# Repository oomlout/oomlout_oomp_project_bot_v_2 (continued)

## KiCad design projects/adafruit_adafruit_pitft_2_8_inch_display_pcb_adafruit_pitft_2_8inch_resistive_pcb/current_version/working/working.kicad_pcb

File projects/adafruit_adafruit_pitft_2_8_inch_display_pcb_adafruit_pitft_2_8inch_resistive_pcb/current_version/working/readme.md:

# adafruit_pitft_2_8_inch_display_pcb
 
## summary 
* id: adafruit_adafruit_pitft_2_8_inch_display_pcb_adafruit_pitft_2_8inch_resistive_pcb
* user: adafruit
* name: adafruit_pitft_2_8_inch_display_pcb
* board: adafruit_pitft_2_8inch_resistive_pcb
* repo: https://github.com/adafruit/Adafruit-PiTFT-2.8-inch-Display-PCB

* src_file_repo_sch: 
* src_file_repo_sch_link: https://github.com/adafruit/Adafruit-PiTFT-2.8-inch-Display-PCB/tree/master/
* full details link: https://github.com/oomlout/oomlout_oomp_project_bot_v_2/tree/main/projects/adafruit_adafruit_pitft_2_8_inch_display_pcb_adafruit_pitft_2_8inch_resistive_pcb/current_version/working  

## schematic  
  
[schematic (pdf)](working_schematic.pdf) 

## pcb  

[board (pdf)](working.pdf)  

## working_bom
| Id | Designator | Footprint | Quantity | Designation | Supplier and ref |  | None | 
| --- | --- | --- | --- | --- | --- | --- | --- | 
| 1 | C3,C2,C4 | C0805K | 3 | 0.1uF |  |  | [''] | 
| 2 | R6,R7,R8 | R0805 | 3 | 10K |  |  | [''] | 
| 3 | Q1 | SOT23-BEC | 1 | MMBT2222 |  |  | [''] | 
| 4 | R11,R10 | R0805 | 2 | 22 |  |  | [''] | 
| 5 | R1,R3,R2,R4 | R0805 | 4 | 100 |  |  | [''] | 
| 6 | C5,C1 | C0805K | 2 | 10uF |  |  | [''] | 
| 7 | IC4 | SOT23-5L | 1 | MIC5225-3.3 |  |  | [''] | 
| 8 | U$10,U$11,U$18 | FIDUCIAL_1MM | 3 | FIDUCIAL |  |  | [''] | 
| 9 | R9,R5 | R0805 | 2 | 1K |  |  | [''] | 
| 10 | U2 | QFN16_3MM | 1 | STMPE610 |  |  | [''] | 
| 11 | IC5 | SOT23 | 1 | AXP803 |  |  | [''] | 
| 12 | JP1 | 2X13 | 1 |  |  |  | [''] | 
| 13 | U$16,U$17,U$15 | MOUNTINGHOLE_2.5_PLATED_THICK | 3 | MOUNTINGHOLE2.5_THICK |  |  | [''] | 
| 14 | U$2 | TFT_2.83IN_240X320_50PIN | 1 | DISP_LCD_1.28IN_240X320_50PIN |  |  | [''] | 
| 15 | SW1,SW2,SW4,SW3 | TACT_PANA-EVQ | 4 |  |  |  | [''] | 
| 16 | U$3 | RASPBERRYPIV2_SHIELD | 1 | RASPBERRYPI_B_MODELB_V2 |  |  | [''] | 
| 17 | U$23 | ADAFRUIT_TEXT_20MM | 1 |  |  |  | [''] | 

## bom_schematic
| Ref | Qnty | Value | Cmp name | Footprint | Description | Vendor | DNP | 
| --- | --- | --- | --- | --- | --- | --- | --- | 
| C1, C5 | 2 | 10uF | C-USC0805K | working:C0805K |  |  |  | 
| C2, C3, C4 | 3 | 0.1uF | C-USC0805K | working:C0805K |  |  |  | 
| IC4 | 1 | LP298XS | LP298XS | working:SOT23-5L |  |  |  | 
| IC5 | 1 | AXP803 | AXP083-SAG | working:SOT23 |  |  |  | 
| JP1 | 1 | HEADER-2X13 | HEADER-2X13 | working:2X13 |  |  |  | 
| Q1 | 1 | MMBT2222 | -NPN-SOT23-BEC | working:SOT23-BEC |  |  |  | 
| R1, R2, R3, R4 | 4 | 100 | R-US_R0805 | working:R0805 |  |  |  | 
| R5, R9 | 2 | 1K | R-US_R0805 | working:R0805 |  |  |  | 
| R6, R7, R8 | 3 | 10K | R-US_R0805 | working:R0805 |  |  |  | 
| R10, R11 | 2 | 22 | R-US_R0805 | working:R0805 |  |  |  | 
| SW1, SW2, SW3, SW4 | 4 | SWITCH_PUSHBUTTONEVQ-PE | SWITCH_PUSHBUTTONEVQ-PE | working:TACT_PANA-EVQ |  |  |  | 
| U2 | 1 | STMPE610 | STMPE610 | working:QFN16_3MM |  |  |  | 
| U$2 | 1 | DISP_LCD_1.28IN_240X320_50PIN | DISP_LCD_1.28IN_240X320_50PIN | working:TFT_2.83IN_240X320_50PIN |  |  |  | 
| U$3 | 1 | RASPBERRYPI_B_MODELB_V2 | RASPBERRYPI_B_MODELB_V2 | working:RASPBERRYPIV2_SHIELD |  |  |  | 
| U$10, U$11, U$18 | 3 | FIDUCIAL | FIDUCIAL | working:FIDUCIAL_1MM |  |  |  | 
| U$15, U$16, U$17 | 3 | MOUNTINGHOLE2.5_THICK | MOUNTINGHOLE2.5_THICK | working:MOUNTINGHOLE_2.5_PLATED_THICK |  |  |  |

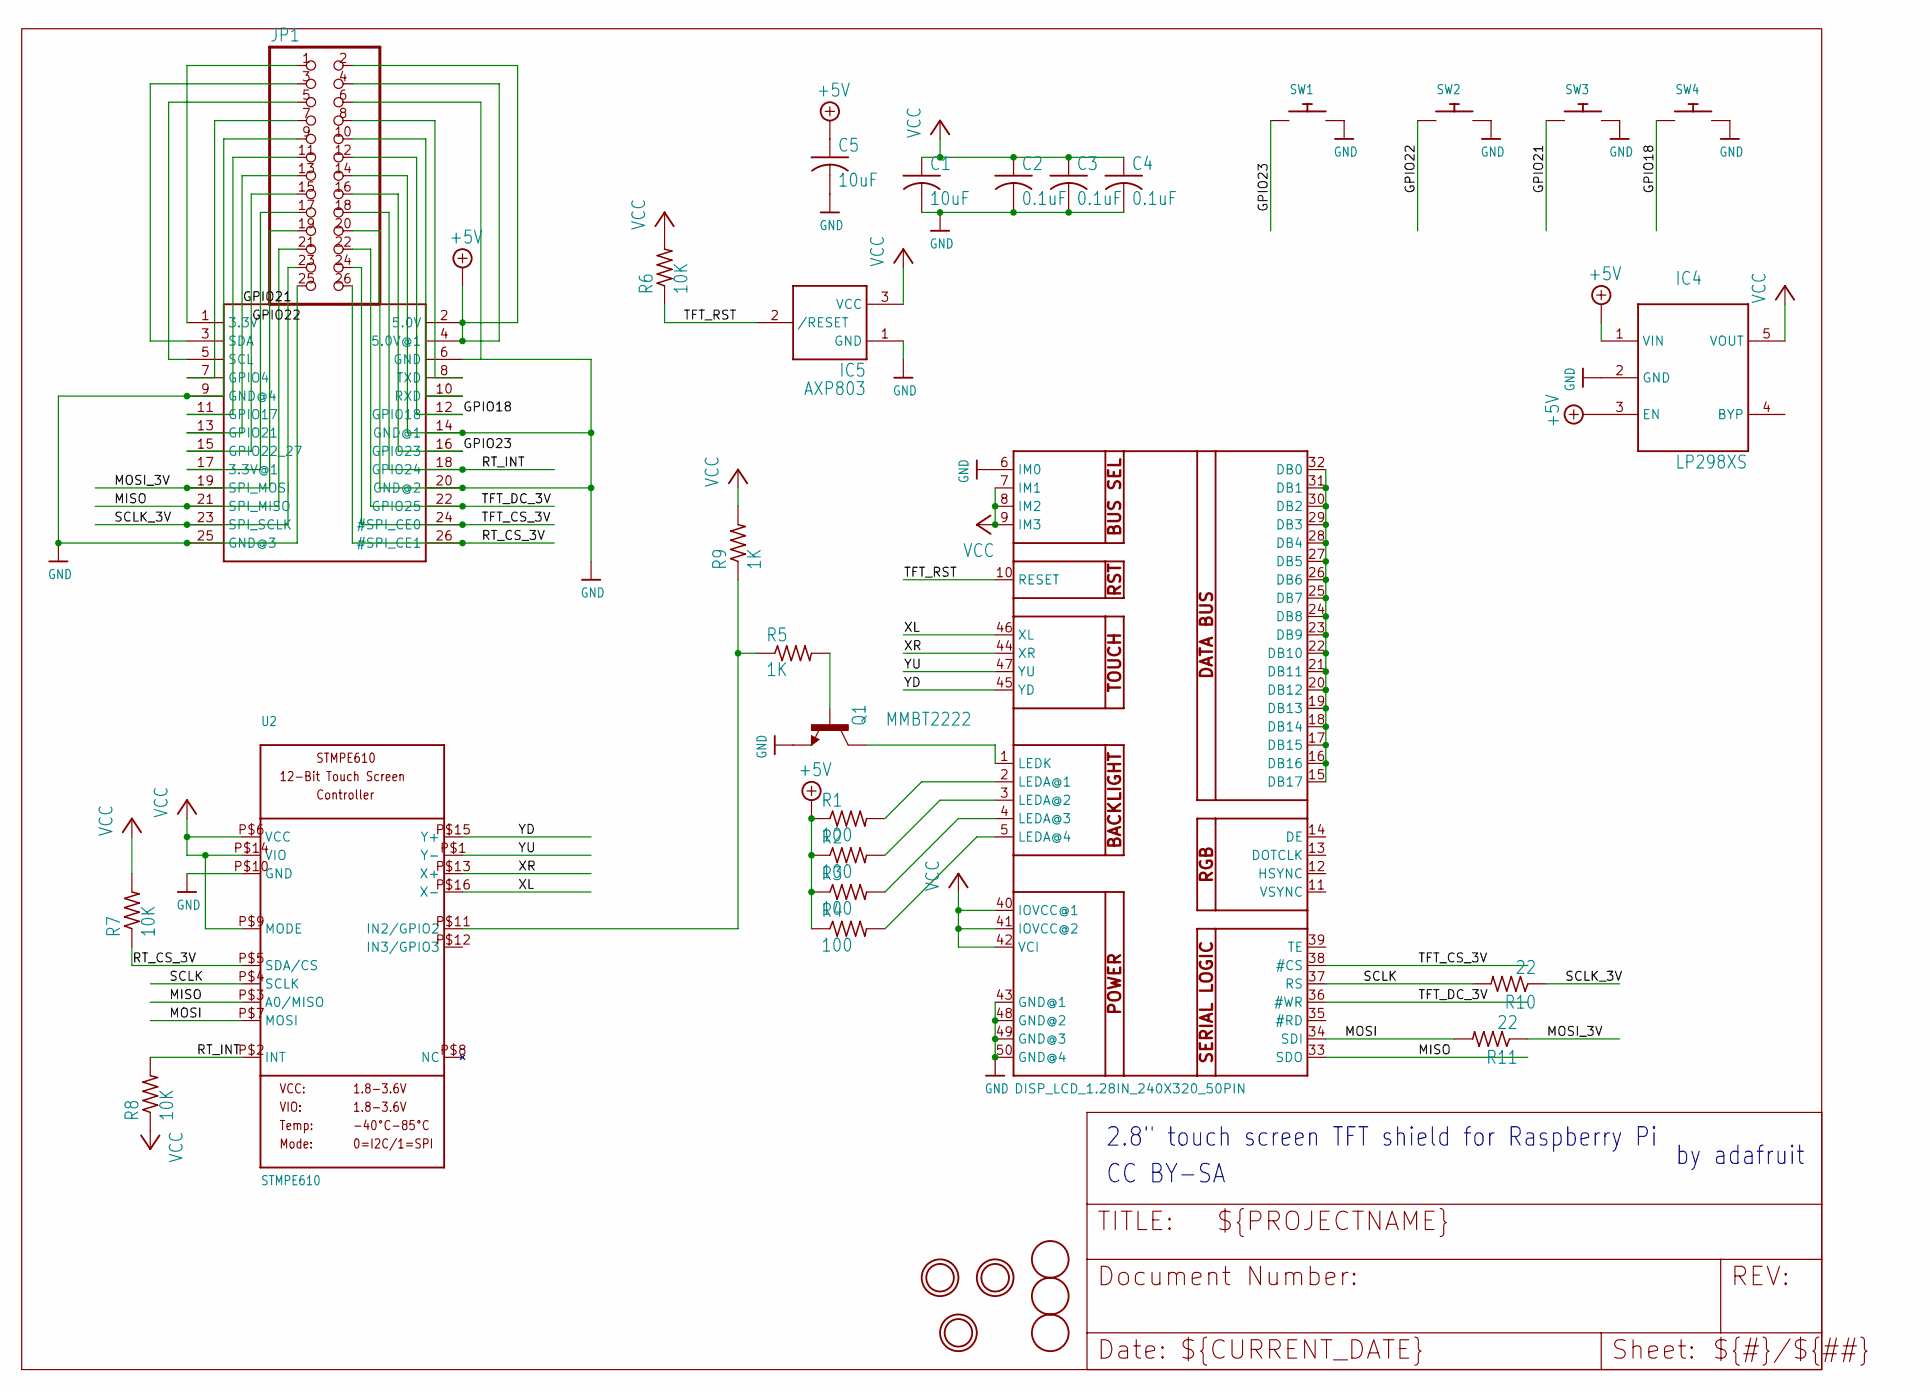
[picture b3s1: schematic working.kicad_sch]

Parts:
C1, C5: 10uF; C0805K
C2, C3, C4: 0.1uF; C0805K
IC4: LP298XS; SOT23-5L
IC5: AXP803; SOT23
JP1: HEADER-2X13; 2X13
Q1: MMBT2222; SOT23-BEC
R1, R2, R3, R4: 100; R0805
R5, R9: 1K; R0805
R6, R7, R8: 10K; R0805
R10, R11: 22; R0805
SW1, SW2, SW3, SW4: SWITCH_PUSHBUTTONEVQ-PE; TACT_PANA-EVQ
U2: STMPE610; QFN16_3MM
U$2: DISP_LCD_1.28IN_240X320_50PIN; TFT_2.83IN_240X320_50PIN
U$3: RASPBERRYPI_B_MODELB_V2; RASPBERRYPIV2_SHIELD
U$10, U$11, U$18: FIDUCIAL; FIDUCIAL_1MM
U$15, U$16, U$17: MOUNTINGHOLE2.5_THICK; MOUNTINGHOLE_2.5_PLATED_THICK

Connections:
3.3V: JP1.1, U$3.1 (3.3V)
3.3V@2: JP1.17, U$3.17 (3.3V@1)
+5V: C5.1, IC4.1 (VIN), IC4.3 (EN), JP1.2, JP1.4, R1.1, R2.1, R3.1, R4.1, U$3.2 (5.0V), U$3.4 (5.0V@1)
GND: C1.2, C2.2, C3.2, C4.2, C5.2, IC4.2 (GND), IC5.1 (GND), JP1.6, JP1.9, JP1.14, JP1.20, JP1.25, Q1.E, SW1.P$2, SW2.P$2, SW3.P$2, SW4.P$2, U2.P$10 (GND), U$2.6 (IM0), U$2.43 (GND@1), U$2.48 (GND@2), U$2.49 (GND@3), U$2.50 (GND@4), U$3.6 (GND), U$3.9 (GND@4), U$3.14 (GND@1), U$3.20 (GND@2), U$3.25 (GND@3)
GPIO18: JP1.12, SW4.P$1, U$3.12 (GPIO18)
GPIO21: JP1.13, SW3.P$1, U$3.13 (GPIO21)
GPIO22: JP1.15, SW2.P$1, U$3.15 (GPIO22_27)
GPIO23: JP1.16, SW1.P$1, U$3.16 (GPIO23)
MISO: JP1.21, U2.P$3 (A0/MISO), U$2.33 (SDO), U$3.21 (SPI_MISO)
MOSI: R11.2, U2.P$7 (MOSI), U$2.34 (SDI)
MOSI_3V: JP1.19, R11.1, U$3.19 (SPI_MOSI)
unnamed: Q1.C, U$2.1 (LEDK)
unnamed: R1.2, U$2.2 (LEDA@1)
unnamed: R2.2, U$2.3 (LEDA@2)
unnamed: R3.2, U$2.4 (LEDA@3)
unnamed: R5.1, R9.1, U2.P$11 (IN2/GPIO2)
unnamed: JP1.3, U$3.3 (SDA)
unnamed: JP1.5, U$3.5 (SCL)
unnamed: JP1.7, U$3.7 (GPIO4)
unnamed: U$2.15 (DB17), U$2.16 (DB16), U$2.17 (DB15), U$2.18 (DB14), U$2.19 (DB13), U$2.20 (DB12), U$2.21 (DB11), U$2.22 (DB10), U$2.23 (DB9), U$2.24 (DB8), U$2.25 (DB7), U$2.26 (DB6), U$2.27 (DB5), U$2.28 (DB4), U$2.29 (DB3), U$2.30 (DB2), U$2.31 (DB1), U$2.32 (DB0)
unnamed: R4.2, U$2.5 (LEDA@4)
unnamed: JP1.11, U$3.11 (GPIO17)
unnamed: Q1.B, R5.2
unnamed: JP1.10, U$3.10 (RXD)
unnamed: JP1.8, U$3.8 (TXD)
RT_CS_3V: JP1.26, R7.1, U2.P$5 (SDA/CS), U$3.26 (#SPI_CE1)
RT_INT: JP1.18, R8.2, U2.P$2 (INT), U$3.18 (GPIO24)
SCLK: R10.2, U2.P$4 (SCLK), U$2.37 (RS)
SCLK_3V: JP1.23, R10.1, U$3.23 (SPI_SCLK)
TFT_CS_3V: JP1.24, U$2.38 (#CS), U$3.24 (#SPI_CE0)
TFT_DC_3V: JP1.22, U$2.36 (#WR), U$3.22 (GPIO25)
TFT_RST: IC5.2 (/RESET), R6.1, U$2.10 (RESET)
VCC: C1.1, C2.1, C3.1, C4.1, IC4.5 (VOUT), IC5.3 (VCC), R6.2, R7.2, R8.1, R9.2, U2.P$6 (VCC), U2.P$9 (MODE), U2.P$14 (VIO), U$2.7 (IM1), U$2.8 (IM2), U$2.9 (IM3), U$2.40 (IOVCC@1), U$2.41 (IOVCC@2), U$2.42 (VCI)
XL: U2.P$16 (X-), U$2.46 (XL)
XR: U2.P$13 (X+), U$2.44 (XR)
YD: U2.P$15 (Y+), U$2.45 (YD)
YU: U2.P$1 (Y-), U$2.47 (YU)

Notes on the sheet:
CC BY-SA
by adafruit~{}
2.8" touch screen TFT shield for Raspberry Pi

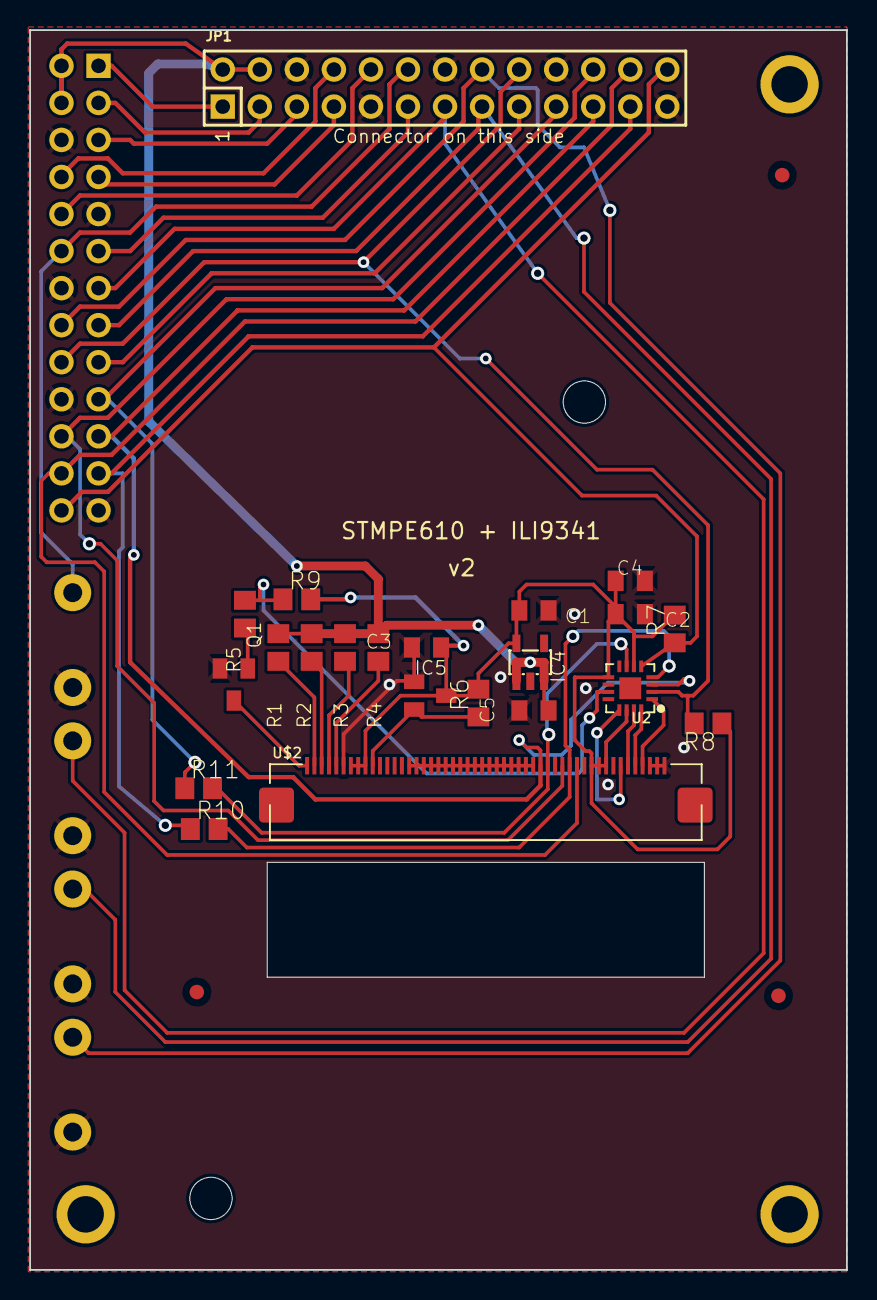
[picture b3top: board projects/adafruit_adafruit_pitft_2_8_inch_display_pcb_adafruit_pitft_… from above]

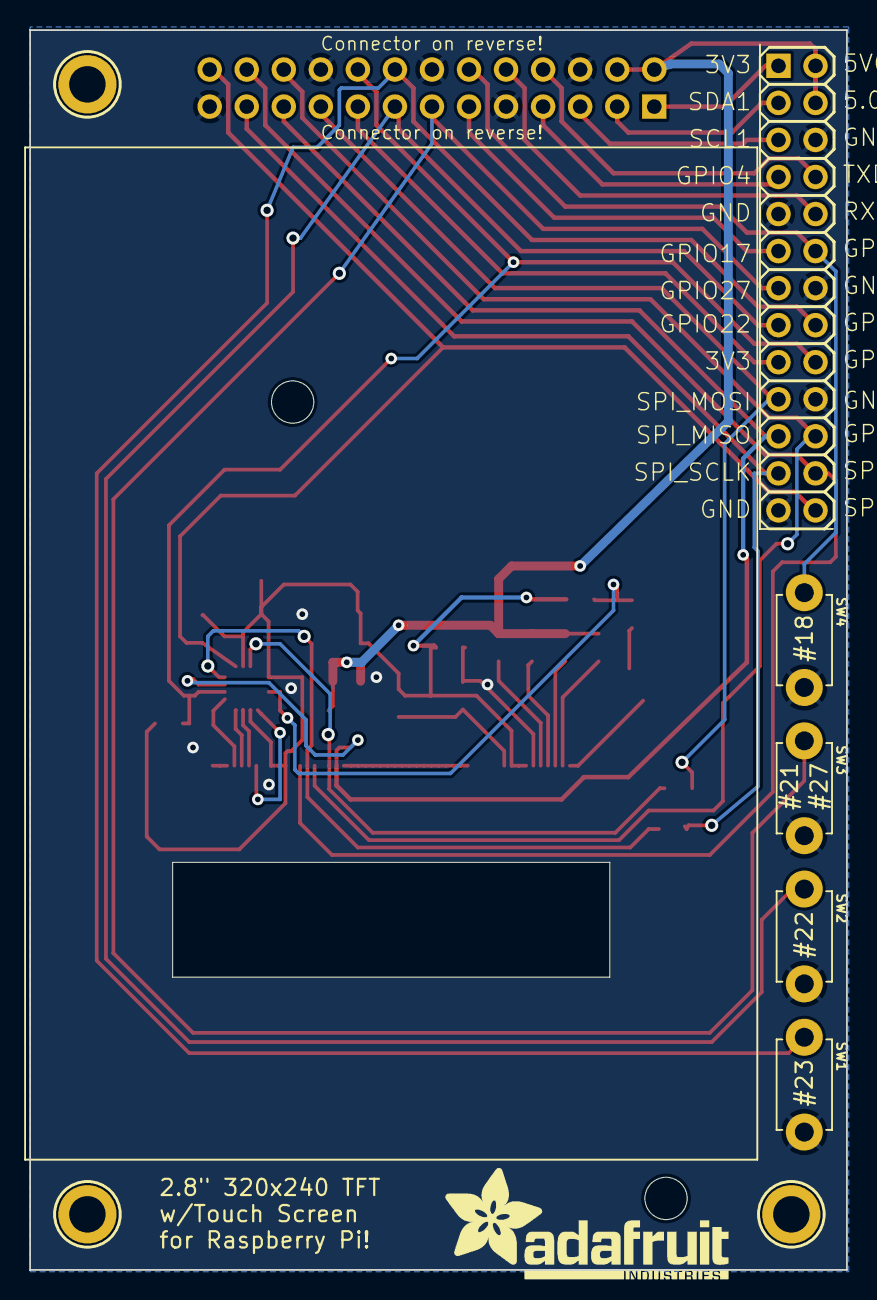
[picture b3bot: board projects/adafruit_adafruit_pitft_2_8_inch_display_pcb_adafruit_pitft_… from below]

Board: 16 copper layers, 56.0 x 85.0 mm, 34 parts (10 on the bottom side), 37 nets.

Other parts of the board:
U$23: ADAFRUIT_TEXT_20MM

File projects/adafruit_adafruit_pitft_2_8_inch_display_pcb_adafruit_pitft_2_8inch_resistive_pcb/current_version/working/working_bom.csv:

"Id";"Designator";"Footprint";"Quantity";"Designation";"Supplier and ref";
1;"C3,C2,C4";"C0805K";3;"0.1uF";;;
2;"R6,R7,R8";"R0805";3;"10K";;;
3;"Q1";"SOT23-BEC";1;"MMBT2222";;;
4;"R11,R10";"R0805";2;"22";;;
5;"R1,R3,R2,R4";"R0805";4;"100";;;
6;"C5,C1";"C0805K";2;"10uF";;;
7;"IC4";"SOT23-5L";1;"MIC5225-3.3";;;
8;"U$10,U$11,U$18";"FIDUCIAL_1MM";3;"FIDUCIAL";;;
9;"R9,R5";"R0805";2;"1K";;;
10;"U2";"QFN16_3MM";1;"STMPE610";;;
11;"IC5";"SOT23";1;"AXP803";;;
12;"JP1";"2X13";1;"";;;
13;"U$16,U$17,U$15";"MOUNTINGHOLE_2.5_PLATED_THICK";3;"MOUNTINGHOLE2.5_THICK";;;
14;"U$2";"TFT_2.83IN_240X320_50PIN";1;"DISP_LCD_1.28IN_240X320_50PIN";;;
15;"SW1,SW2,SW4,SW3";"TACT_PANA-EVQ";4;"";;;
16;"U$3";"RASPBERRYPIV2_SHIELD";1;"RASPBERRYPI_B_MODELB_V2";;;
17;"U$23";"ADAFRUIT_TEXT_20MM";1;"";;;

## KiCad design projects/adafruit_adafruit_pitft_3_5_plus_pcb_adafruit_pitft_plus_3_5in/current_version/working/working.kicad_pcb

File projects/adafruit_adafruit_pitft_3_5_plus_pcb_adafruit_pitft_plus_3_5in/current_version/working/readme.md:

# adafruit_pitft_3_5_plus_pcb
 
## summary 
* id: adafruit_adafruit_pitft_3_5_plus_pcb_adafruit_pitft_plus_3_5in
* user: adafruit
* name: adafruit_pitft_3_5_plus_pcb
* board: adafruit_pitft_plus_3_5in
* repo: https://github.com/adafruit/Adafruit-PiTFT-3.5-Plus-PCB

* src_file_repo_sch: 
* src_file_repo_sch_link: https://github.com/adafruit/Adafruit-PiTFT-3.5-Plus-PCB/tree/master/
* full details link: https://github.com/oomlout/oomlout_oomp_project_bot_v_2/tree/main/projects/adafruit_adafruit_pitft_3_5_plus_pcb_adafruit_pitft_plus_3_5in/current_version/working  

## schematic  
  
[schematic (pdf)](working_schematic.pdf) 

## pcb  

[board (pdf)](working.pdf)  

## working_bom
| Id | Designator | Footprint | Quantity | Designation | Supplier and ref |  | None | 
| --- | --- | --- | --- | --- | --- | --- | --- | 
| 1 | U2 | QFN16_3MM | 1 | STMPE610 |  |  | [''] | 
| 2 | @HOLE20,@HOLE17,@HOLE3,@HOLE23,@HOLE21,@HOLE26,@HOLE14,@HOLE12,@HOLE8,@HOLE2,@HOLE27,@HOLE10,@HOLE5,@HOLE13,@HOLE22,@HOLE0,@HOLE25,@HOLE15,@HOLE6,@HOLE11,@HOLE19,@HOLE9,@HOLE18,@HOLE1,@HOLE16,@HOLE7,@HOLE24,@HOLE4 |  | 28 |  |  |  | [''] | 
| 3 | C1,C16 | 0805-NO | 2 | 10uF |  |  | [''] | 
| 4 | U3 | SOT23-5@1 | 1 | FAN5333BSX |  |  | [''] | 
| 5 | R2,R11,R5,R6,R7 | 0805-NO | 5 | 10K |  |  | [''] | 
| 6 | GPIO26,GPIO5,GPIO20,GPIO21,GPIO6,GPIO16,GPIO12,GPIO13,GPIO19 | PAD-1.5X2.0 | 9 |  |  |  | [''] | 
| 7 | D2 | SOD-123 | 1 | MBR0540 |  |  | [''] | 
| 8 | U1 | SOIC8_150MIL | 1 | CAT24C32 |  |  | [''] | 
| 9 | L1 | INDUCTOR_1007 | 1 | 10uH 1007 |  |  | [''] | 
| 10 | R10 | 0805-NO | 1 | 1K |  |  | [''] | 
| 11 | D1 | SMADIODE | 1 | MM3Z24VT1G |  |  | [''] | 
| 12 | U$23 | ADAFRUIT_TEXT_20MM | 1 |  |  |  | [''] | 
| 13 | U$10,U$11,U$18 | FIDUCIAL_1MM | 3 | FIDUCIAL" |  |  | [''] | 
| 14 | R13,R12,R14 | 0805-NO | 3 | 3.9K |  |  | [''] | 
| 15 | SJ2 | SOLDERJUMPER_CLOSEDWIRE | 1 |  |  |  | [''] | 
| 16 | C20 | _0805MP | 1 | 1uF |  |  | [''] | 
| 17 | IC5 | SOT23 | 1 | AXP803 |  |  | [''] | 
| 18 | R4 | 0805-NO | 1 | 12 |  |  | [''] | 
| 19 | C4,C18 | 0805-NO | 2 | 0.1uF |  |  | [''] | 
| 20 | SJ1 | SOLDERJUMPER_CLOSEDWIRE | 1 | WP |  |  | [''] | 
| 21 | R8 | 0805-NO | 1 | DNP |  |  | [''] | 
| 22 | R1 | 0805-NO | 1 | 12â„¦ |  |  | [''] | 
| 23 | R9 | _0805MP | 1 | 1K |  |  | [''] | 
| 24 | U$19 | PCBFEAT-REV-056 | 1 |  |  |  | [''] | 
| 25 | R3 | _0805MP | 1 | 12 |  |  | [''] | 
| 26 | JP1 | 2X13_SMT_MALE | 1 |  |  |  | [''] | 
| 27 | X1 | TFT_3.5IN_320X480_50PIN | 1 |  |  |  | [''] | 
| 28 | U$20,U$15,U$17,U$16 | MOUNTINGHOLE_2.5_PLATED_THICK | 4 | MOUNTINGHOLE2.5_THICK |  |  | [''] | 
| 29 | RPI1 | RASPBERRYPI_BPLUS_SHIELD_SMT | 1 | RASPBERRYPI_BPLUS_SMT |  |  | [''] | 

## bom_schematic
| Ref | Qnty | Value | Cmp name | Footprint | Description | Vendor | DNP | 
| --- | --- | --- | --- | --- | --- | --- | --- | 
| C1, C16 | 2 | 10uF | CAP_CERAMIC0805-NOOUTLINE | working:0805-NO |  |  |  | 
| C4, C18 | 2 | 0.1uF | CAP_CERAMIC0805-NOOUTLINE | working:0805-NO |  |  |  | 
| C20 | 1 | 1uF | CAP_CERAMIC_0805MP | working:_0805MP |  |  |  | 
| D1 | 1 | MM3Z24VT1G | DIODESMA | working:SMADIODE |  |  |  | 
| D2 | 1 | MBR0540 | DIODESOD-123 | working:SOD-123 |  |  |  | 
| GPIO5, GPIO6, GPIO12, GPIO13, GPIO16, GPIO19, GPIO20, GPIO21, GPIO26 | 9 | TESTPOINT1.5X2.0MM_NOCREAM | TESTPOINT1.5X2.0MM_NOCREAM | working:PAD-1.5X2.0 |  |  |  | 
| IC5 | 1 | AXP803 | AXP083-SAG | working:SOT23 |  |  |  | 
| JP1 | 1 | HEADER-2X13-SMT | HEADER-2X13-SMT | working:2X13_SMT_MALE |  |  |  | 
| L1 | 1 | 10uH 1007 | INDUCTOR | working:INDUCTOR_1007 |  |  |  | 
| R1 | 1 | 12â„¦ | RESISTOR0805_NOOUTLINE | working:0805-NO |  |  |  | 
| R2, R5, R6, R7, R11 | 5 | 10K | RESISTOR0805_NOOUTLINE | working:0805-NO |  |  |  | 
| R3 | 1 | 12 | RESISTOR_0805MP | working:_0805MP |  |  |  | 
| R4 | 1 | 12 | RESISTOR0805_NOOUTLINE | working:0805-NO |  |  |  | 
| R8 | 1 | DNP | RESISTOR0805_NOOUTLINE | working:0805-NO |  |  |  | 
| R9 | 1 | 1K | RESISTOR_0805MP | working:_0805MP |  |  |  | 
| R10 | 1 | 1K | RESISTOR0805_NOOUTLINE | working:0805-NO |  |  |  | 
| R12, R13, R14 | 3 | 3.9K | RESISTOR0805_NOOUTLINE | working:0805-NO |  |  |  | 
| RPI1 | 1 | RASPBERRYPI_BPLUS_SMT | RASPBERRYPI_BPLUS_SMT | working:RASPBERRYPI_BPLUS_SHIELD_SMT |  |  |  | 
| SJ1 | 1 | WP | SOLDERJUMPER_CLOSED | working:SOLDERJUMPER_CLOSEDWIRE |  |  |  | 
| SJ2 | 1 | SOLDERJUMPERCLOSED | SOLDERJUMPERCLOSED | working:SOLDERJUMPER_CLOSEDWIRE |  |  |  | 
| U1 | 1 | CAT24C32 | EEPROM_I2C_SOIC8_GENERIC | working:SOIC8_150MIL |  |  |  | 
| U2 | 1 | STMPE610 | STMPE610 | working:QFN16_3MM |  |  |  | 
| U3 | 1 | FAN5333BSX | FAN5331 | working:SOT23-5@1 |  |  |  | 
| U$10, U$11, U$18 | 3 | FIDUCIAL"" | FIDUCIAL{dblquote}{dblquote} | working:FIDUCIAL_1MM |  |  |  | 
| U$15, U$16, U$17, U$20 | 4 | MOUNTINGHOLE2.5_THICK | MOUNTINGHOLE2.5_THICK | working:MOUNTINGHOLE_2.5_PLATED_THICK |  |  |  | 
| X1 | 1 | DISP_LCD_3.5IN_320X480_50PIN | DISP_LCD_3.5IN_320X480_50PIN | working:TFT_3.5IN_320X480_50PIN |  |  |  |

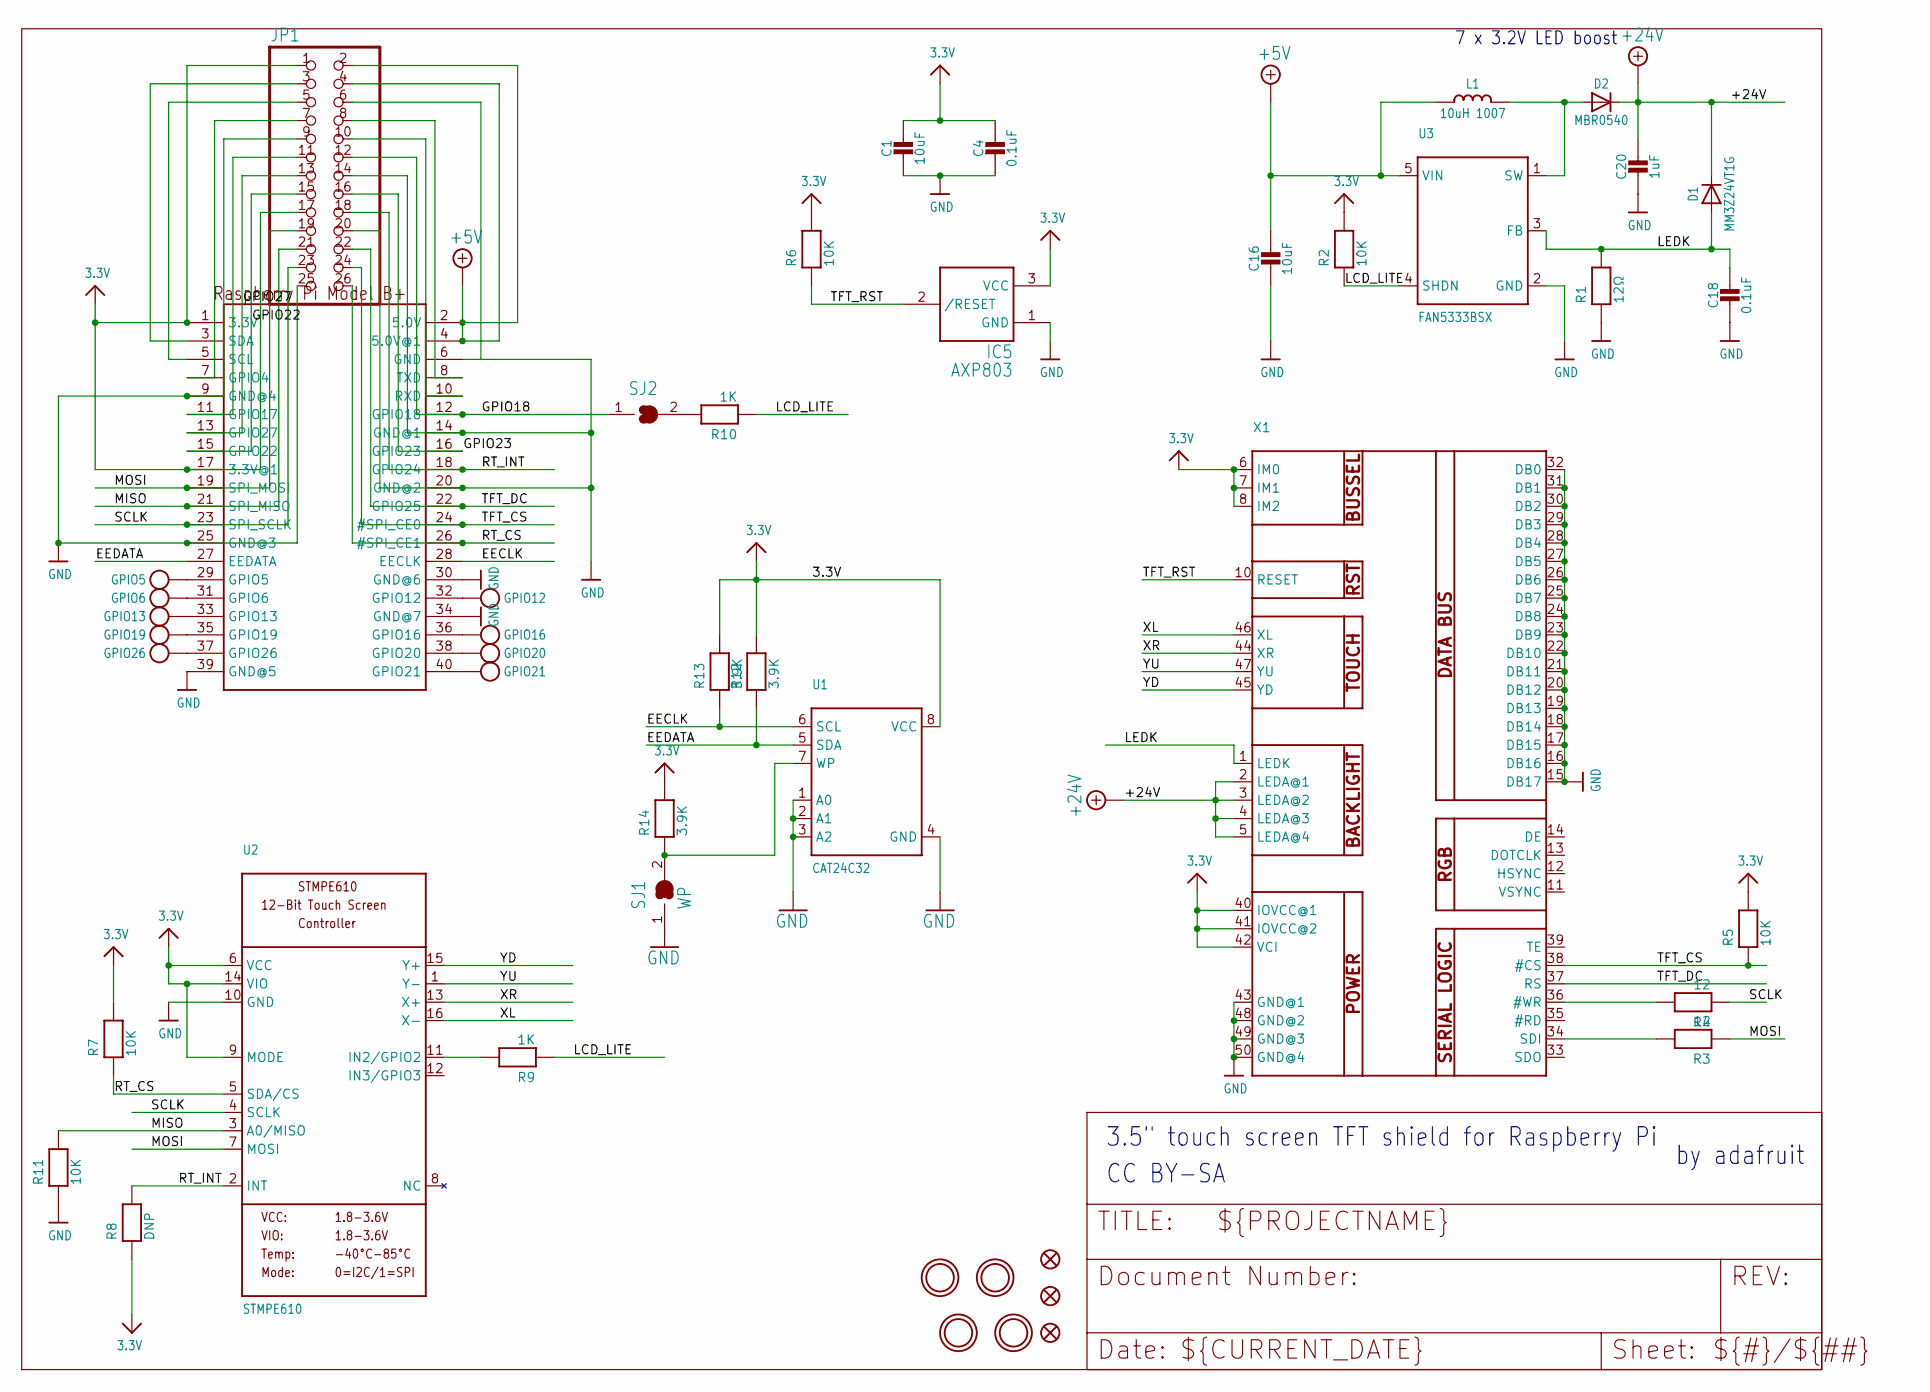
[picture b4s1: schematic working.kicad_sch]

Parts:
C1, C16: 10uF; 0805-NO
C4, C18: 0.1uF; 0805-NO
C20: 1uF; _0805MP
D1: MM3Z24VT1G; SMADIODE
D2: MBR0540; SOD-123
GPIO5, GPIO6, GPIO12, GPIO13, GPIO16, GPIO19, GPIO20, GPIO21, GPIO26: TESTPOINT1.5X2.0MM_NOCREAM; PAD-1.5X2.0
IC5: AXP803; SOT23
JP1: HEADER-2X13-SMT; 2X13_SMT_MALE
L1: 10uH 1007; INDUCTOR_1007
R1: 12Ω; 0805-NO
R2, R5, R6, R7, R11: 10K; 0805-NO
R3: 12; _0805MP
R4: 12; 0805-NO
R8: DNP; 0805-NO
R9: 1K; _0805MP
R10: 1K; 0805-NO
R12, R13, R14: 3.9K; 0805-NO
RPI1: RASPBERRYPI_BPLUS_SMT; RASPBERRYPI_BPLUS_SHIELD_SMT
SJ1: WP; SOLDERJUMPER_CLOSEDWIRE
SJ2: SOLDERJUMPERCLOSED; SOLDERJUMPER_CLOSEDWIRE
U1: CAT24C32; SOIC8_150MIL
U2: STMPE610; QFN16_3MM
U3: FAN5333BSX; SOT23-5@1
U$10, U$11, U$18: FIDUCIAL""; FIDUCIAL_1MM
U$15, U$16, U$17, U$20: MOUNTINGHOLE2.5_THICK; MOUNTINGHOLE_2.5_PLATED_THICK
X1: DISP_LCD_3.5IN_320X480_50PIN; TFT_3.5IN_320X480_50PIN

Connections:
3.3V: C1.1, C4.1, IC5.3 (VCC), JP1.1, JP1.17, R2.2, R5.2, R6.2, R7.2, R8.1, R12.2, R13.2, R14.2, RPI1.1 (3.3V), RPI1.17 (3.3V@1), U1.8 (VCC), U2.6 (VCC), U2.9 (MODE), U2.14 (VIO), X1.6 (IM0), X1.7 (IM1), X1.8 (IM2), X1.40 (IOVCC@1), X1.41 (IOVCC@2), X1.42 (VCI)
+5V: C16.1, JP1.2, JP1.4, L1.P$1 (1), RPI1.2 (5.0V), RPI1.4 (5.0V@1), U3.5 (VIN)
+24V: C20.1, D1.C, D2.C, X1.2 (LEDA@1), X1.3 (LEDA@2), X1.4 (LEDA@3), X1.5 (LEDA@4)
EECLK: R13.1, RPI1.28 (EECLK), U1.6 (SCL)
EEDATA: R12.1, RPI1.27 (EEDATA), U1.5 (SDA)
GND: C1.2, C4.2, C16.2, C18.2, C20.2, IC5.1 (GND), JP1.6, JP1.9, JP1.14, JP1.20, JP1.25, R1.1, R11.1, RPI1.6 (GND), RPI1.9 (GND@4), RPI1.14 (GND@1), RPI1.20 (GND@2), RPI1.25 (GND@3), RPI1.30 (GND@6), RPI1.34 (GND@7), RPI1.39 (GND@5), SJ1.1, U1.1 (A0), U1.2 (A1), U1.3 (A2), U1.4 (GND), U2.10 (GND), U3.2 (GND), X1.15 (DB17), X1.16 (DB16), X1.17 (DB15), X1.18 (DB14), X1.19 (DB13), X1.20 (DB12), X1.21 (DB11), X1.22 (DB10), X1.23 (DB9), X1.24 (DB8), X1.25 (DB7), X1.26 (DB6), X1.27 (DB5), X1.28 (DB4), X1.29 (DB3), X1.30 (DB2), X1.31 (DB1), X1.32 (DB0), X1.43 (GND@1), X1.48 (GND@2), X1.49 (GND@3), X1.50 (GND@4)
GPIO6: GPIO6.P$1, RPI1.31 (GPIO6)
GPIO16: GPIO16.P$1, RPI1.36 (GPIO16)
GPIO18: JP1.12, RPI1.12 (GPIO18), SJ2.1
GPIO22: JP1.15, RPI1.15 (GPIO22)
GPIO23: JP1.16, RPI1.16 (GPIO23)
GPIO27: JP1.13, RPI1.13 (GPIO27)
LCD_LITE: R2.1, R9.1, R10.1, U3.4 (SHDN)
LEDK: C18.1, D1.A, R1.2, U3.3 (FB), X1.1 (LEDK)
MISO: JP1.21, R11.2, RPI1.21 (SPI_MISO), U2.3 (A0/MISO)
MOSI: JP1.19, R3.1, RPI1.19 (SPI_MOSI), U2.7 (MOSI)
unnamed: R4.2, X1.36 (#WR)
unnamed: R3.2, X1.34 (SDI)
unnamed: R9.2, U2.11 (IN2/GPIO2)
unnamed: R10.2, SJ2.2
unnamed: GPIO5.P$1, RPI1.29 (GPIO5)
unnamed: JP1.3, RPI1.3 (SDA)
unnamed: JP1.5, RPI1.5 (SCL)
unnamed: JP1.7, RPI1.7 (GPIO4)
unnamed: GPIO13.P$1, RPI1.33 (GPIO13)
unnamed: GPIO19.P$1, RPI1.35 (GPIO19)
unnamed: JP1.11, RPI1.11 (GPIO17)
unnamed: D2.A, L1.P$2 (2), U3.1 (SW)
unnamed: GPIO26.P$1, RPI1.37 (GPIO26)
unnamed: GPIO12.P$1, RPI1.32 (GPIO12)
unnamed: GPIO20.P$1, RPI1.38 (GPIO20)
unnamed: R14.1, SJ1.2, U1.7 (WP)
unnamed: JP1.10, RPI1.10 (RXD)
unnamed: JP1.8, RPI1.8 (TXD)
unnamed: GPIO21.P$1, RPI1.40 (GPIO21)
RT_CS: JP1.26, R7.1, RPI1.26 (#SPI_CE1), U2.5 (SDA/CS)
RT_INT: JP1.18, R8.2, RPI1.18 (GPIO24), U2.2 (INT)
SCLK: JP1.23, R4.1, RPI1.23 (SPI_SCLK), U2.4 (SCLK)
TFT_CS: JP1.24, R5.1, RPI1.24 (#SPI_CE0), X1.38 (#CS)
TFT_DC: JP1.22, RPI1.22 (GPIO25), X1.37 (RS)
TFT_RST: IC5.2 (/RESET), R6.1, X1.10 (RESET)
XL: U2.16 (X-), X1.46 (XL)
XR: U2.13 (X+), X1.44 (XR)
YD: U2.15 (Y+), X1.45 (YD)
YU: U2.1 (Y-), X1.47 (YU)

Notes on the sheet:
7 x 3.2V LED boost
by adafruit~{}
3.5" touch screen TFT shield for Raspberry Pi
CC BY-SA

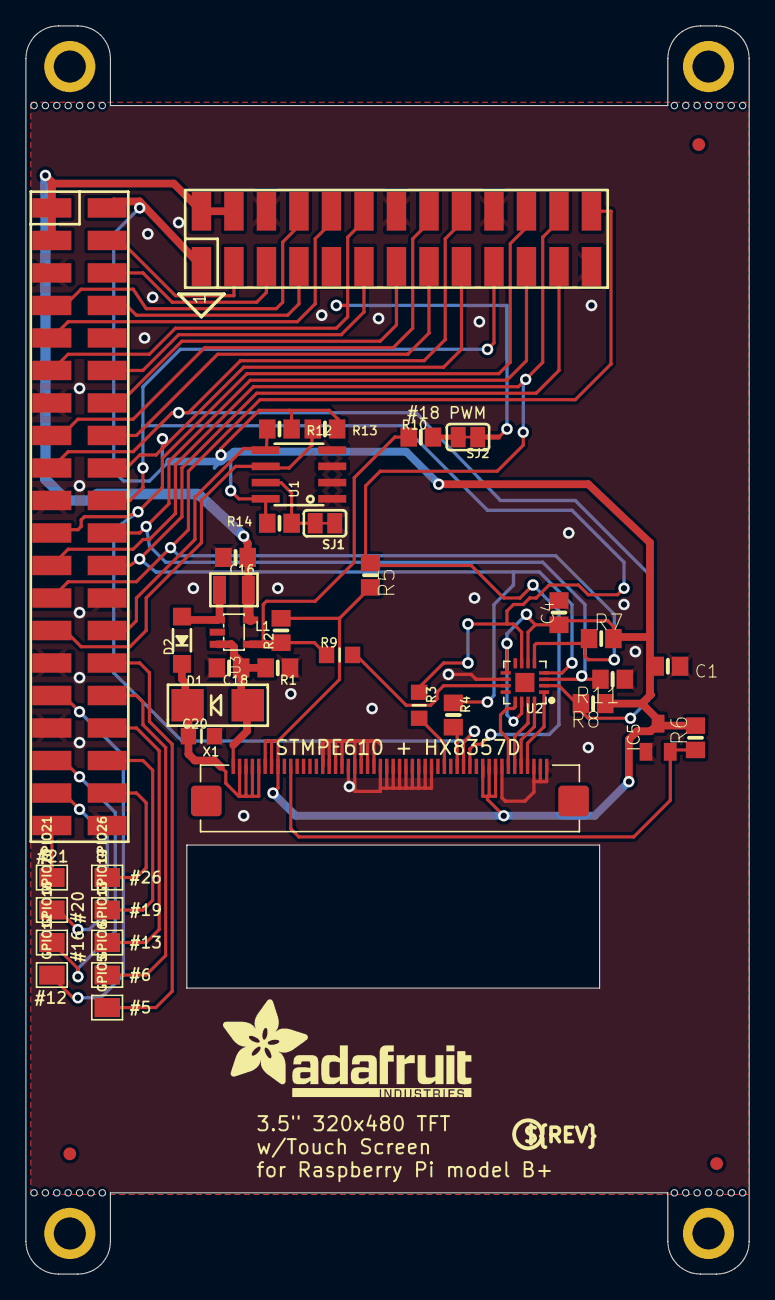
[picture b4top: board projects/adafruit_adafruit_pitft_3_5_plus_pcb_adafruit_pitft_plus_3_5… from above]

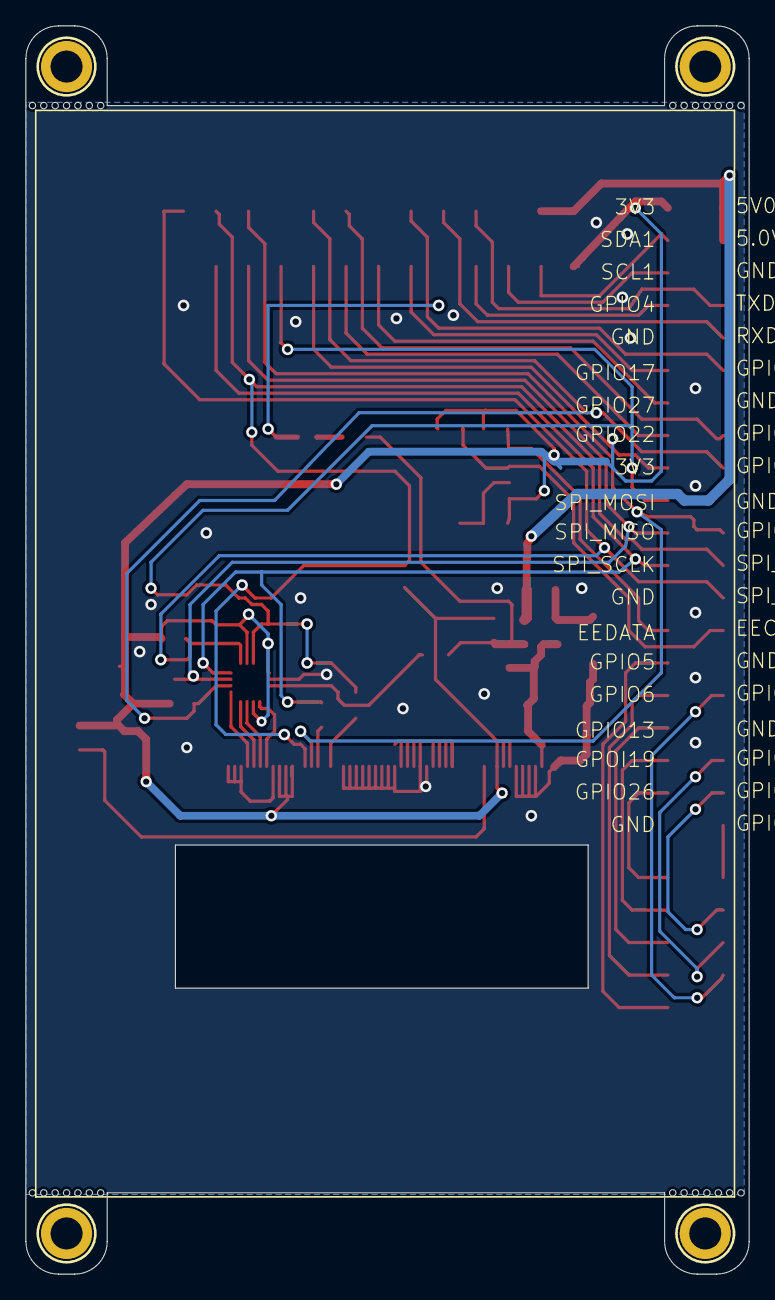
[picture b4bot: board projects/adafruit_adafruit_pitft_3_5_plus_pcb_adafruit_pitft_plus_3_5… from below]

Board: 16 copper layers, 56.5 x 97.5 mm, 77 parts (6 on the bottom side), 45 nets.

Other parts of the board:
@HOLE0, @HOLE1, @HOLE2, @HOLE3, @HOLE4, @HOLE5, @HOLE6, @HOLE7, @HOLE8, @HOLE9, @HOLE10, @HOLE11, @HOLE12, @HOLE13, @HOLE14, @HOLE15, @HOLE16, @HOLE17, @HOLE18, @HOLE19, @HOLE20, @HOLE21, @HOLE22, @HOLE23, @HOLE24, @HOLE25, @HOLE26, @HOLE27: (no value)
U$19: PCBFEAT-REV-056
U$23: ADAFRUIT_TEXT_20MM

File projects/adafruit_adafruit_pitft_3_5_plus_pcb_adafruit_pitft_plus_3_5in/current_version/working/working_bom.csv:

"Id";"Designator";"Footprint";"Quantity";"Designation";"Supplier and ref";
1;"U2";"QFN16_3MM";1;"STMPE610";;;
2;"@HOLE20,@HOLE17,@HOLE3,@HOLE23,@HOLE21,@HOLE26,@HOLE14,@HOLE12,@HOLE8,@HOLE2,@HOLE27,@HOLE10,@HOLE5,@HOLE13,@HOLE22,@HOLE0,@HOLE25,@HOLE15,@HOLE6,@HOLE11,@HOLE19,@HOLE9,@HOLE18,@HOLE1,@HOLE16,@HOLE7,@HOLE24,@HOLE4";"";28;"";;;
3;"C1,C16";"0805-NO";2;"10uF";;;
4;"U3";"SOT23-5@1";1;"FAN5333BSX";;;
5;"R2,R11,R5,R6,R7";"0805-NO";5;"10K";;;
6;"GPIO26,GPIO5,GPIO20,GPIO21,GPIO6,GPIO16,GPIO12,GPIO13,GPIO19";"PAD-1.5X2.0";9;"";;;
7;"D2";"SOD-123";1;"MBR0540";;;
8;"U1";"SOIC8_150MIL";1;"CAT24C32";;;
9;"L1";"INDUCTOR_1007";1;"10uH 1007";;;
10;"R10";"0805-NO";1;"1K";;;
11;"D1";"SMADIODE";1;"MM3Z24VT1G";;;
12;"U$23";"ADAFRUIT_TEXT_20MM";1;"";;;
13;"U$10,U$11,U$18";"FIDUCIAL_1MM";3;"FIDUCIAL""";;;
14;"R13,R12,R14";"0805-NO";3;"3.9K";;;
15;"SJ2";"SOLDERJUMPER_CLOSEDWIRE";1;"";;;
16;"C20";"_0805MP";1;"1uF";;;
17;"IC5";"SOT23";1;"AXP803";;;
18;"R4";"0805-NO";1;"12";;;
19;"C4,C18";"0805-NO";2;"0.1uF";;;
20;"SJ1";"SOLDERJUMPER_CLOSEDWIRE";1;"WP";;;
21;"R8";"0805-NO";1;"DNP";;;
22;"R1";"0805-NO";1;"12Ω";;;
23;"R9";"_0805MP";1;"1K";;;
24;"U$19";"PCBFEAT-REV-056";1;"";;;
25;"R3";"_0805MP";1;"12";;;
26;"JP1";"2X13_SMT_MALE";1;"";;;
27;"X1";"TFT_3.5IN_320X480_50PIN";1;"";;;
28;"U$20,U$15,U$17,U$16";"MOUNTINGHOLE_2.5_PLATED_THICK";4;"MOUNTINGHOLE2.5_THICK";;;
29;"RPI1";"RASPBERRYPI_BPLUS_SHIELD_SMT";1;"RASPBERRYPI_BPLUS_SMT";;;
